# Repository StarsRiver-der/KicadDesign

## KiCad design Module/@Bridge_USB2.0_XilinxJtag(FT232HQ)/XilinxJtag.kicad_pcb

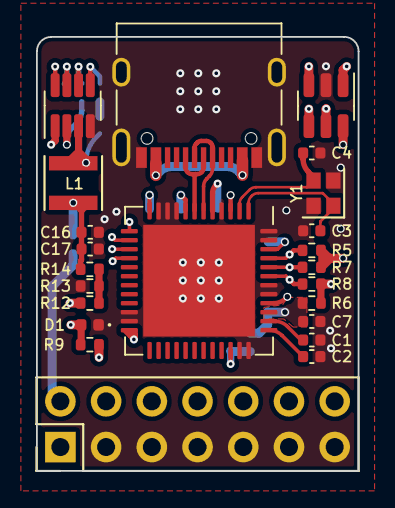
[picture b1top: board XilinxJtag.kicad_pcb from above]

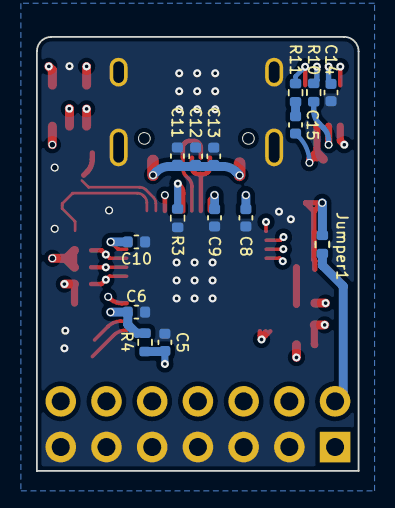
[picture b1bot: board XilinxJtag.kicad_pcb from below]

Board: 4 copper layers, 17.9 x 24.1 mm, 38 parts (15 on the bottom side), 29 nets.

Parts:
C1, C2, C5, C7, C9, C10, C12, C14, C15: 0.1uF; C_0402_1005Metric
C3, C4: 27pF; C_0402_1005Metric
C6, C8, C11, C13, C16, C17: 10uF; C_0402_1005Metric
D1: LED; LED_0402_1005Metric
J1: USB-C16PSMT01; USB_C_Receptacle_XKB_U262-16XN-4BVC11
J2: Conn_01x06_Male; PinHeader_2x07_P2.54mm_Vertical
Jumper1: Jumper; R_0402_1005Metric
L1: 4.7uF; L_Taiyo-Yuden_NR-30xx
R3: 12K; R_0402_1005Metric
R4, R5, R6, R7: 10K; R_0402_1005Metric
R8: 2K; R_0402_1005Metric
R9: 3K; R_0402_1005Metric
R10: 1M; R_0402_1005Metric
R11: 20R; R_0402_1005Metric
R12: 51K; R_0402_1005Metric
R13: 13K; R_0402_1005Metric
R14: 41.2K; R_0402_1005Metric
U1: FT232H; QFN-48-1EP_8x8mm_P0.5mm_EP6.2x6.2mm
U2: 93LC56BxxOT; SOT-23-6
U3: mp9442; TSOT-23-8
Y1: 12M; Crystal_SMD_2016-4Pin_2.0x1.6mm

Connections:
3.3V: C16.1, C17.1, Jumper1.2, L1.2, R14.1
+3V3: C6.1, C7.1, C8.1, C9.1, C10.1, R4.2, R5.1, R6.1, R7.1, U1.3 (VPHY), U1.8 (VPLL), U1.12 (VCCIO), U1.24 (VCCIO), U1.39 (VCCD), U1.46 (VCCIO), U2.6 (VCC)
DM: J1.A7 (DN1), J1.B7 (DN2), U1.6 (DM)
DP: J1.A6 (DP1), J1.B6 (DP2), U1.7 (DP)
EEP_CLK: R7.2, U1.44 (EECLK), U2.4 (CLK)
EEP_CS: R5.2, U1.45 (EECS), U2.5 (CS)
EEP_D: R8.2, U1.43 (EEDATA), U2.3 (DI)
unnamed: C1.1, U1.38 (VCCCORE)
unnamed: C2.1, U1.37 (VCCA)
unnamed: C3.2, U1.1 (XCSI), Y1.1
unnamed: C4.2, U1.2 (XCSO), Y1.3
unnamed: C14.1, U3.7 (VCC)
unnamed: C15.1, R11.1
unnamed: C15.2, L1.1, U3.3 (SW)
unnamed: D1.2 (A), R9.1, U3.1 (PG)
unnamed: J2.2, Jumper1.1
unnamed: R3.1, U1.5 (REF)
unnamed: R6.2, R8.1, U2.1 (DO)
unnamed: R10.1, U3.6 (EN)
unnamed: R11.2, U3.5 (BST)
unnamed: R12.1, R13.2, R14.2
unnamed: R12.2, U3.8 (FB)
RESET: C5.1, R4.1, U1.34 (~RESET)
TCK: J2.6, U1.13 (ADBUS0)
TDI: J2.10, U1.14 (ADBUS1)
TDO: J2.8, U1.15 (ADBUS2)
TMS: J2.4, U1.16 (ADBUS3)
VBUS: C11.1, C12.1, C13.1, J1.A4 (VBUS), J1.A9 (VBUS), J1.B4 (VBUS), J1.B9 (VBUS), R9.2, R10.2, U1.40 (VREGIN), U3.2 (IN)
VSS: C1.2, C2.2, C3.1, C4.1, C5.2, C6.2, C7.2, C8.2, C9.2, C10.2, C11.2, C12.2, C13.2, C14.2, C16.2, C17.2, D1.1 (K), J1.A1 (GND), J1.A12 (GND), J1.B1 (GND), J1.B12 (GND), J1.S1 (SHIELD), J2.3, J2.5, J2.7, J2.9, J2.11, J2.13, R3.2, R13.1, U1.4 (AGND), U1.9 (AGND), U1.10 (GND), U1.11 (GND), U1.22 (GND), U1.23 (GND), U1.35 (GND), U1.36 (GND), U1.41 (AGND), U1.42 (TEST), U1.47 (GND), U1.48 (GND), U1.49 (EP), U2.2 (GND), U3.4 (GND), Y1.2, Y1.4

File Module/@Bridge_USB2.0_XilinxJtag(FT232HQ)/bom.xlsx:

标号 | 数量/板 | 值 | 备注 | 封装 | 数量 | 单价 | 总价
C1, C2, C5, C7, C9, C10, C12, C14, C15 | 9 | 0.1uF |  | 0402 | 100 | 0 | 0
C3, C4 | 2 | 27pF |  | 0402 | 100 | 0 | 0
C6, C8, C11, C13, C16, C17 | 6 | 10uF |  | 0402 | 100 | 0 | 0
D1 | 1 | LED |  | 0402 | 100 | 0 | 0
L1 | 1 | 4.7uF |  | NR3015 | 20 | 0 | 0
R0 | 1 | 0R |  | 0402 | 100 | 0 | 0
R3 | 1 | 12K |  | 0402 | 100 | 0 | 0
R4, R5, R6, R7 | 4 | 10K |  | 0402 | 100 | 0 | 0
R8 | 1 | 2K |  | 0402 | 100 | 0 | 0
R9 | 1 | 3K |  | 0402 | 100 | 0 | 0
R10 | 1 | 1M |  | 0402 | 100 | 0 | 0
R11 | 1 | 20R |  | 0402 | 100 | 0 | 0
R12 | 1 | 51K |  | 0402 | 100 | 0 | 0
R13 | 1 | 13K |  | 0402 | 100 | 0 | 0
R14 | 1 | 41.2K |  | 0402 | 100 | 0 | 0
J1 | 1 | USB-C16PSMT01 |  | TypeC-16pin | 10 | 0 | 0
J2 | 1 | 简牛母座 14pin |  | 2.54mm, 2x7pin | 10 | 0 | 0
U1 | 1 | FT232H |  | QFN-48 | 2 | 0 | 0
U2 | 1 | 93LC56B-I/OT |  | SOT-23-6 | 5 | 0 | 0
U3 | 1 | mp9442 |  | TSOT-23-8 | 5 | 0 | 0
Y1 | 1 | 12M |  | 2Pin_2.0x1.2mm | 5 | 0 | 0

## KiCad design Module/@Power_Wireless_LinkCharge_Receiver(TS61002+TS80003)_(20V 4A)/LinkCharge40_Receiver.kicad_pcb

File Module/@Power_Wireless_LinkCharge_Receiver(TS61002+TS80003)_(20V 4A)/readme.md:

# LinkCharge无线充电接收器
提供QI1.2-15W，LinkCharge40W功率输出

# 接口
* 无线输入：Pin_5mm_2P
* 电压输出：PogoPin_4.8mm_4P

# 预览

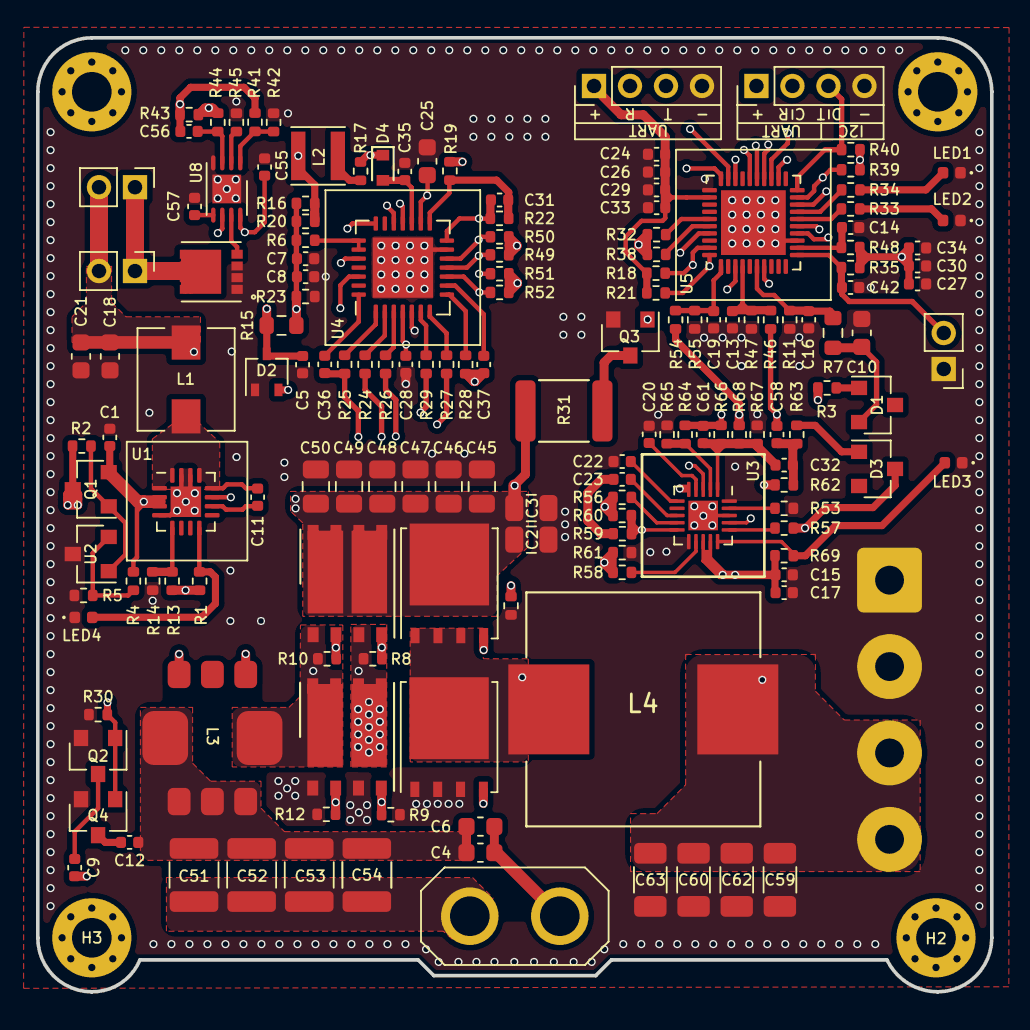
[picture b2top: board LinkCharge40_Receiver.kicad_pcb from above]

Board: 4 copper layers, 53.0 x 53.0 mm, 163 parts (0 on the bottom side), 91 nets.

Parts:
C1, C15, C20: 1uF 50V; C_0402_1005Metric
C2, C3, C45, C46, C48, C49: 22uF 50V; C_0805_2012Metric
C4, C6: 1nF 250V NP; C_0603_1608Metric
C5: 10pF 50V; C_0402_1005Metric
C7, C13, C14, C16, C17, C19, C23, C26, C28, C29, C30, C33, C42: 100nF 50V; C_0402_1005Metric
C8, C24, C27, C35: 4.7uF 25V; C_0402_1005Metric
C9, C12: 15nF 50V; C_0402_1005Metric
C10: 1nF 250V; C_0603_1608Metric
C11, C36, C37: 47nF 50V; C_0402_1005Metric
C18, C21: 22uF 16V; C_0603_1608Metric
C22: 10nF 50V; C_0402_1005Metric
C25: 10uF 25V; C_0603_1608Metric
C31: 47pF 50V; C_0402_1005Metric
C32: 1nF 50V; C_0402_1005Metric
C34: 4.7nF 100V; C_0402_1005Metric
C47, C50: 100nF 250V; C_0805_2012Metric
C51, C52: 47nF 250V; C_1210_3225Metric
C53: 10nF 250V NP; C_1210_3225Metric
C54: NP; C_1210_3225Metric
C55: 4.7uF; C_0402_1005Metric
C56: 1uF; C_0402_1005Metric
C57: 330nF; C_0402_1005Metric
C58: 22nF 50V; C_0402_1005Metric
C59, C60, C62, C63: 10uF; C_1206_3216Metric
C61: 330pF; C_0402_1005Metric
D1: BAS101S,215; SOT-23
D2: BAT54SW; SOT-323_SC-70
D3: BAS21; SOT-23
D4: 1N5819WT; D_SOD-523
H1, H2, H3, H4: MountingHole; MountingHole_2.2mm_M2_Pad_Via
J1, J6, J7: Conn_01x02_Male; PinHeader_1x02_P2.00mm_Vertical
J2, J3: I2C; PinHeader_1x04_P2.00mm_Vertical
J4: I2C; SolderWire-0.75sqmm_1x04_P4.8mm_D1.25mm_OD2.3mm
J5: COIL 24uH; AMASS_XT30U-F_1x02_P5.0mm_Vertical
L1: 4.7uH; L_Wuerth_HCI-5040
L2: 1uF; L_Taiyo-Yuden_NR-30xx
L3: PA1005.100NLT; PA1005
L4: 22uH; L_Wuerth_HCI-1350
LED1, LED2, LED3, LED4: LED; LED_0402_1005Metric
NCP15XW153J03RC1: Thermistor_NTC; R_0402_1005Metric
Q1, Q2, Q3, Q4: 2N7002; SOT-23
Q5: BSC100N06L; TDSON-8-1
Q6: BSC028N06L; TDSON-8-1
R1, R69: 5.1K; R_0402_1005Metric
R2, R5, R14, R18, R19, R21, R22, R32, R35, R39, R40, R47, R48, R55, R57, R62: 10K; R_0402_1005Metric
R3, R20, R23: 7.5K; R_0402_1005Metric
R4, R54: 133K; R_0402_1005Metric
R6, R25, R28, R49, R50, R51, R52: 0R; R_0402_1005Metric
R7: 100K; R_0603_1608Metric
R8, R9, R10, R12, R60, R61: 20K; R_0402_1005Metric
R11: 1.5K; R_0402_1005Metric
R13: 47K; R_0402_1005Metric
R15: 20R; R_0603_1608Metric
R16, R42: 200K; R_0402_1005Metric
R17, R24, R26, R27, R29, R56, R58: 1R; R_0402_1005Metric
R30: 100K; R_0402_1005Metric
R31: 200R; R_1812_4532Metric
R33, R34: 150R; R_0402_1005Metric
R38: 4.7K; R_0402_1005Metric
R41: 33K; R_0402_1005Metric
R43, R45: 12.4K; R_0402_1005Metric
R44: 5.1M; R_0402_1005Metric
R46: 75K; R_0402_1005Metric
R53: 715K; R_0402_1005Metric
R59: 3R3; R_0402_1005Metric
R63: 4.99K; R_0402_1005Metric
R64: 9.09K; R_0402_1005Metric
R65, R67: 1K; R_0402_1005Metric
R66: 34K; R_0402_1005Metric
R68: 499K; R_0402_1005Metric
U1: TS30041; QFN-16-1EP_3x3mm_P0.5mm_EP1.7x1.7mm
U2: TL431DBZ; SOT-23
U3: SC506; QFN-20-1EP_3x3mm_P0.4mm_EP1.65x1.65mm
U4: TS61002; QFN-28-1EP_5x5mm_P0.5mm_EP3.35x3.35mm
U5: TS80003; QFN-40-1EP_5x5mm_P0.4mm_EP3.6x3.6mm
U6, U7: IPG20N06S4L-11; Infineon_PG-TISON-8-2-2
U8: max31740; TDFN-8-1EP_3x2mm_P0.5mm_EP1.80x1.65mm
U9: CSD16406Q3

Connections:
+3V3: C24.1, C26.1, C29.1, C33.1, D2.2, D4.1 (K), J2.1, J3.1, R17.1, R18.1, R21.1, R39.1, R40.1, U5.15 (VDD), U5.32 (VDD)
+5V: C15.2, C17.2, C18.1, C21.1, C25.1, C28.1, C55.1, C56.1, J6.2, J7.2, L1.2, R1.2, R13.2, R41.2, R43.1, R69.2, U3.3 (VDDA), U3.13 (VDDP), U3.14 (PSV), U4.4 (VCCG), U4.16 (LDO_EN), U8.6 (D0), U8.8 (VDD)
ACMPREF: C14.1, R48.1, U5.12 (ACMPREF)
AC_I: C16.1, R7.1, R11.1, U5.6 (AC_I)
AC_I_1: R19.1, U4.19 (RA), U5.7 (AC_I_1)
AC_I_2: C31.2, R22.2, U4.14 (VOUTA), U5.3 (AC_I_2)
COIL-: C51.1, C52.1, C53.1, C54.1, J5.1, R3.2
DC_V: C13.2, R46.1, R47.2, U5.4 (DC_V)
EN_DRV: U4.26 (DRV_EN), U5.18 (DRV_EN)
EN_GAIN: R32.2, R38.2, U4.24 (GAIN)
EN_LOAD: U3.17 (EN), U5.26 (EN_LOAD)
EN_MOD: Q2.1 (G), Q4.1 (G), R30.1, U5.25 (EN_MOD)
GND: C1.2, C2.1, C3.1, C5.1, C7.2, C8.2, C10.2, C13.1, C14.2, C15.1, C16.2, C17.1, C18.2, C19.1, C20.1, C21.2, C22.1, C24.2, C25.2, C26.2, C27.2, C28.2, C29.2, C30.2, C33.2, C34.2, C35.2, C42.2, C45.1, C46.1, C47.1, C48.1, C49.1, C50.1, C55.2, C57.2, C59.1, C60.1, C62.1, C63.1, D2.1, J1.1, J2.4, J3.4, J4.1, J4.2, LED1.1 (K), LED2.1 (K), LED3.1 (K), LED4.1 (K), NCP15XW153J03RC1.2, Q2.2 (S), Q3.2 (S), Q4.2 (S), Q6.1 (S), Q6.2 (S), Q6.3 (S), R5.2, R9.1, R11.2, R12.1, R14.1, R23.1, R30.2, R42.1, R45.2, R47.1, R53.1, R55.1, R61.2, R65.2, R67.2, U1.4 (GND), U1.14 (GND), U1.15 (GND), U1.17 (GND), U2.3 (A), U3.11 (PGND), U3.18 (AGND), U3.20 (ENL), U3.21 (EP), U4.5 (PGND), U4.13 (AGND), U4.29 (PAD), U5.13 (AVSS), U5.31 (VSS), U5.41 (PAD), U7.1, U7.3, U8.4 (GND), U8.9 (EP), U9.1, U9.2, U9.3
HT: C2.2, C3.2, C45.2, C46.2, C47.2, C48.2, C49.2, C50.2, Q1.3 (D), Q5.5 (D), R2.1, R31.1, R54.2, R68.2, U3.5 (VIN), U6.5, U6.6, U6.7, U6.8
ISENSE: C5.2, D2.3, L3.3, R15.2, U4.21 (VIN)
MIN_LD: Q3.1 (G), U5.37 (EN_MINLD)
unnamed: C1.1, Q1.2 (S), R4.1, U1.2 (VCC), U1.3 (VCC), U1.11 (VCC)
unnamed: C9.2, Q2.3 (D)
unnamed: C10.1, D1.2, R7.2
unnamed: C11.1, U1.10 (BST)
unnamed: C11.2, L1.1, U1.1 (VSW), U1.12 (VSW), U1.13 (VSW), U1.16 (VSW)
unnamed: C12.2, Q4.3 (D)
unnamed: C20.2, U3.4 (VLDO)
unnamed: C22.2, U3.6 (SS)
unnamed: C23.1, U3.8 (BST)
unnamed: C23.2, R59.2
unnamed: C31.1, R19.2, R22.1, U4.15 (CA)
unnamed: C32.1, C61.1, R66.2, R67.1, R68.1, U3.1 (FB)
unnamed: C32.2, C58.1, R62.1, R63.1
unnamed: C35.1, D4.2 (A), U4.17 (VLDO)
unnamed: C36.1, U4.28 (VB1)
unnamed: C37.1, U4.9 (VB2)
unnamed: C37.2, L3.8, R10.1, R28.2, U6.1, U7.7, U7.8
unnamed: C56.2, R44.2, U8.3 (SENSE)
unnamed: C57.1, U8.5 (FREQ)
unnamed: D1.1, R3.1
unnamed: D3.1 (A), R63.2
unnamed: D3.3 (K), L4.1, Q5.1 (S), Q5.2 (S), Q5.3 (S), Q6.5 (D), R57.1, R59.1, R60.2, R62.2, U3.10 (LX)
unnamed: J2.2, R39.2, U5.19 (I2C|SCL)
unnamed: J2.3, R40.2, U5.20 (I2C|SDA)
unnamed: J3.2, R18.2, U5.39 (BT|RX)
unnamed: J3.3, R21.2, U5.40 (BT|TX)
unnamed: J6.1, J7.1, U9.5, U9.6, U9.7, U9.8
unnamed: L2.2, R17.2
unnamed: LED1.2 (A), R34.2
unnamed: LED2.2 (A), R33.2
unnamed: LED3.2 (A), R69.1, U3.15 (PG)
unnamed: LED4.2 (A), R1.1, U1.8 (PG)
unnamed: NCP15XW153J03RC1.1, R43.2, R44.1
unnamed: Q1.1 (G), R2.2, U2.1 (K)
unnamed: Q3.3 (D), R31.2
unnamed: Q5.4 (G), R56.1, R60.1
unnamed: Q6.4 (G), R58.1, R61.1
unnamed: R4.2, R5.1, U2.2 (REF)
unnamed: R6.1, U4.22 (CB), U4.23 (VOUTB)
unnamed: R10.2, R27.2, U6.2
unnamed: R12.2, R29.2, U7.2
unnamed: R13.1, R14.2, U1.5 (FB)
unnamed: R24.1, U4.2 (HO1)
unnamed: R8.2, R24.2, U6.4
unnamed: R25.1, U4.1 (VS1)
unnamed: R26.1, U4.3 (LO1)
unnamed: R9.2, R26.2, U7.4
unnamed: R27.1, U4.7 (HO2)
unnamed: R28.1, U4.8 (VS2)
unnamed: R29.1, U4.6 (LO2)
unnamed: R32.1, U5.35 (AC_GAIN1)
unnamed: R33.1, U5.16 (LEDG)
unnamed: R34.1, U5.17 (LEDB)
unnamed: R38.1, U5.36 (AC_GAIN2)
unnamed: R41.1, R42.2, U8.1 (Dmin)
unnamed: R45.1, U8.2 (SLOPE)
unnamed: R49.1, R50.1, U5.22 (ACMP1_OUT)
unnamed: R51.1, R52.1, U5.28 (ACMP2_OUT)
unnamed: R53.2, U3.19 (TON)
unnamed: R56.2, U3.9 (DH)
unnamed: R57.2, U3.16 (LIMI)
unnamed: R58.2, U3.12 (DL)
unnamed: R64.2, R65.1, U3.2 (VOUT)
unnamed: U8.7 (PWM_OUT), U9.4
PDC_V: C19.2, R54.1, R55.2, U5.1 (PDC_V)
PWM1_H: R49.2, U4.11 (HS1ON), U5.23 (PWM1|H)
PWM1_L: R52.2, U4.10 (LS1ON), U5.24 (PWM1|L)
PWM2_H: R51.2, U4.18 (HS2ON), U5.30 (PWM2|H)
PWM2_L: R50.2, U4.12 (LS2ON), U5.29 (PWM2|L)
TEMP: C42.1, J1.2, R35.1, U5.11 (TEMP)
VAC1: C4.1, C6.1, C9.1, C36.2, J5.2, R8.1, R25.2, U6.3, U7.5, U7.6
VAC2: C4.2, C6.2, C12.1, C51.2, C52.2, C53.2, C54.2, L3.4, L3.5, L3.6, L3.7
VACC_MID: C7.1, C8.1, L3.1, R6.2, R15.1, R16.1, R20.1, R23.2
VDC: C58.2, C59.2, C60.2, C61.2, C62.2, C63.2, J4.3, J4.4, L4.2, R46.2, R64.1, R66.1
VDDA: C27.1, C30.1, C34.1, L2.1, R16.2, R20.2, R35.2, R48.2, U5.14 (AVDD)

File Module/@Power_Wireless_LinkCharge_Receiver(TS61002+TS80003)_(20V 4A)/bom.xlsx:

标号 | 数量/板 | 值 | 封装 | 数量 | 单价 | 总价
C1, C15, C20 | 3 | 1uF 50V | 0402 | 100 | 0 | 0
C2, C3, C45, C46, C48, C49 | 6 | 22uF 50V | 0805 | 100 | 0 | 0
C4, C6 | 2 | 1nF 250V | 0603 | 100 | 0 | 0
C5 | 1 | 10pF 50V | 0402 | 100 | 0 | 0
C7, C13, C14, C16, C17, C19, C23, C26, C28, C29, C30, C33, C42 | 13 | 100nF 50V | 0402 | 100 | 0 | 0
C8, C24, C27, C35 | 4 | 4.7uF 25V | 0402 | 100 | 0 | 0
C9, C12 | 2 | 15nF 50V | 0402 | 100 | 0 | 0
C10 | 1 | 1nF 250V | 0603 | 100 | 0 | 0
C11, C36, C37 | 3 | 47nF 50V | 0402 | 100 | 0 | 0
C18, C21 | 2 | 22uF 16V | 0603 | 100 | 0 | 0
C22 | 1 | 10nF 50V | 0402 | 100 | 0 | 0
C25 | 1 | 10uF 25V | 0603 | 100 | 0 | 0
C31 | 1 | 47pF 50V | 0402 | 100 | 0 | 0
C32 | 1 | 1nF 50V | 0402 | 100 | 0 | 0
C34 | 1 | 4.7nF 100V | 0402 | 100 | 0 | 0
C47, C50 | 2 | 100nF 250V | 0805 | 100 | 0 | 0
C51, C52 | 2 | 47nF 250V | 1210 | 100 | 0 | 0
C53 | 1 | 10nF 250V | 1210 | 100 | 0 | 0
C54 | 1 | NP | 1210 | 100 | 0 | 0
C55 | 1 | 4.7uF 25V | 0402 | 100 | 0 | 0
C56 | 1 | 1uF 25V | 0402 | 100 | 0 | 0
C57 | 1 | 330nF 25V | 0402 | 100 | 0 | 0
C58 | 1 | 22nF 50V | 0402 | 100 | 0 | 0
C59, C60, C62, C63 | 4 | 10uF 50V | 1206 | 100 | 0 | 0
C61 | 1 | 330pF 50V | 0402 | 100 | 0 | 0
L1 | 1 | 4.7uH | 5040 | 20 | 0 | 0
L2 | 1 | 1uH | 3014 | 20 | 0 | 0
L3 | 1 | PA1005.100NLT | PA1005 | 10 | 0 | 0
L4 | 1 | 22uH | 1250 | 10 | 0 | 0
LED1, LED2, LED3, LED4 | 4 | LED | 0402 | 100 | 0 | 0
R1, R69 | 2 | 5.1K | 0402 | 100 | 0 | 0
R2, R5, R14, R18, R19, R21, R22, R32, R35, R39, R40, R47, R48, R55, R57, R62 | 16 | 10K | 0402 | 100 | 0 | 0
R3, R20, R23 | 3 | 7.5K | 0402 | 100 | 0 | 0
R4, R54 | 2 | 133K | 0402 | 100 | 0 | 0
R6, R25, R28, R49, R50, R51, R52 | 7 | 0R | 0402 | 100 | 0 | 0
R7 | 1 | 100K | 0603 | 100 | 0 | 0
R8, R9, R10, R12, R60, R61 | 6 | 20K | 0402 | 100 | 0 | 0
R11 | 1 | 1.5K | 0402 | 100 | 0 | 0
R13 | 1 | 47K | 0402 | 100 | 0 | 0
R15 | 1 | 20R | 0603 | 100 | 0 | 0
R16, R42 | 2 | 200K | 0402 | 100 | 0 | 0
R17, R24, R26, R27, R29, R56, R58 | 7 | 1R | 0402 | 100 | 0 | 0
R30 | 1 | 100K | 0402 | 100 | 0 | 0
R31 | 1 | 200R | 1812 | 100 | 0 | 0
R33, R34 | 2 | 150R | 0402 | 100 | 0 | 0
R38 | 1 | 4.7K | 0402 | 100 | 0 | 0
R41 | 1 | 33K | 0402 | 100 | 0 | 0
R43, R45 | 2 | 12.4K | 0402 | 100 | 0 | 0
R44 | 1 | 5.1M | 0402 | 100 | 0 | 0
R46 | 1 | 75K | 0402 | 100 | 0 | 0
R53 | 1 | 715K | 0402 | 100 | 0 | 0
R59 | 1 | 3R3 | 0402 | 100 | 0 | 0
R63 | 1 | 4.99K | 0402 | 100 | 0 | 0
R64 | 1 | 9.09K | 0402 | 100 | 0 | 0
R65, R67 | 2 | 1K | 0402 | 100 | 0 | 0
R66 | 1 | 34K | 0402 | 100 | 0 | 0
R68 | 1 | 499K | 0402 | 100 | 0 | 0
TR1 | 1 | NCP15XW153J03RC1 | 0402 | 20 | 0 | 0
D1 | 1 | BAS101S,215 | SOT-23 | 20 | 0 | 0
D2 | 1 | BAT54SW | SOT-323_SC-70 | 20 | 0 | 0
D3 | 1 | BAS21-03W | SOT-23 | 20 | 0 | 0
D4 | 1 | RB521S-30C | SOT-523 | 20 | 0 | 0
Q1, Q2, Q3, Q4 | 4 | 2N7002 | SOT-23 | 20 | 0 | 0
Q5 | 1 | BSC100N06L | TDSON-8-1 | 10 | 0 | 0
Q6 | 1 | BSC028N06L | TDSON-8-1 | 10 | 0 | 0
U2 | 1 | TL431DBZ | SOT-23 | 20 | 0 | 0
U1 | 1 | TS30041 | QFN-16-1EP_3x3mm_P0.5mm | 5 | 0 | 0
U3 | 1 | SC506 | QFN-20-1EP_3x3mm_P0.4mm | 5 | 0 | 0
U4 | 1 | TS61002 | QFN-28-1EP_5x5mm_P0.5mm | 5 | 0 | 0
U5 | 1 | TS80003 | QFN-40-1EP_5x5mm_P0.4mm | 5 | 0 | 0
U6, U7 | 2 | IPG20N06S4L-11 | PG-TISON-8-2-2 | 10 | 0 | 0
U8 | 1 | max31740 | TDFN-8-1EP_3x2mm_P0.5mm | 5 | 0 | 0
U9 | 1 | CSD16406Q3 |  | 5 | 0 | 0

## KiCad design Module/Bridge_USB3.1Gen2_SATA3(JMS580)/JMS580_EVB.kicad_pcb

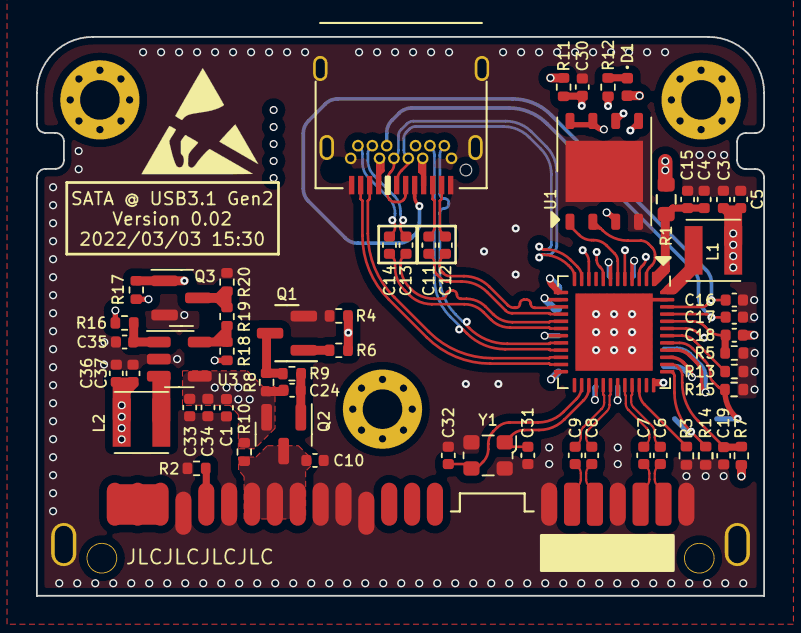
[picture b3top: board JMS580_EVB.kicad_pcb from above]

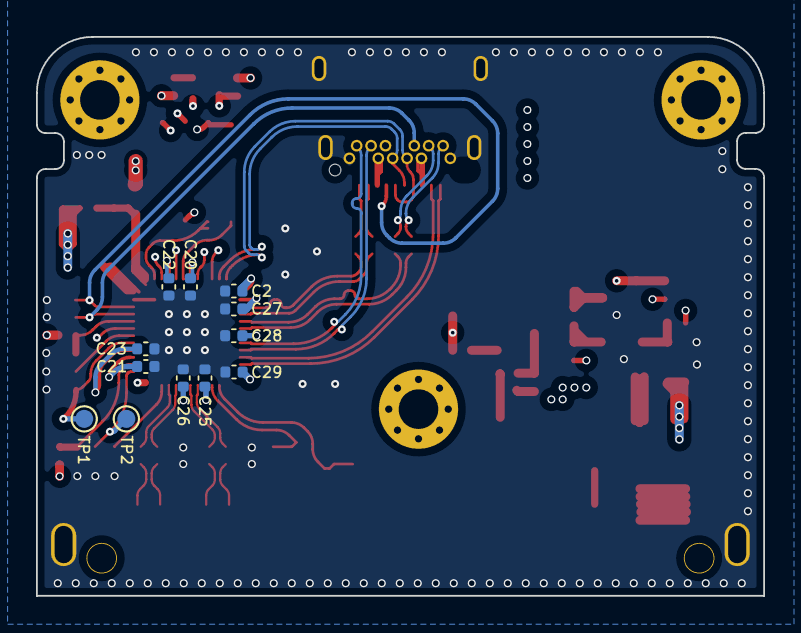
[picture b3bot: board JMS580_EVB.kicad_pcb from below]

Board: 4 copper layers, 40.4 x 31.1 mm, 75 parts (12 on the bottom side), 57 nets.

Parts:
C1, C10: 4.7uF; C_0402_1005Metric
C2, C18, C19, C24, C30, C35: 1uF; C_0402_1005Metric
C3, C4, C5, C33, C36: 10uF; C_0402_1005Metric
C6, C7, C8, C9: 10nF; C_0402_1005Metric
C11, C12, C13, C14, C15, C20, C21, C22, C23, C25, C26, C27, C28, C29, C34, C37: 100nF; C_0402_1005Metric
C16, C17: 330pF; C_0402_1005Metric
C31, C32: 20pF; C_0402_1005Metric
D1: LED; LED_0402_1005Metric
H1, H2, H3: MountingHole; MountingHole_2.2mm_M2_Pad_Via
H4: Symbol; ESD-Logo_6.6x6mm_SilkScreen
J1: ATA-A; SATA-22P-M
J2: USB_C_Receptacle; USB-C_24p
L1: 4R7 / NS; L_Neosid_SMS-ME3015
L2: 3R3; L_Neosid_SMS-ME3015
Q1: MMBT3904LT1G(1AM); SOT-23
Q2: AO3401A; SOT-23
Q3: AO3400A; SOT-23
R1: 0R; R_0603_1608Metric
R2: 10K; R_0402_1005Metric
R3: 12K; R_0402_1005Metric
R4, R5, R6, R13, R17: 4.7K; R_0402_1005Metric
R7, R16, R20: 510K; R_0402_1005Metric
R8, R12: 1K; R_0402_1005Metric
R9: 0R; R_0402_1005Metric
R10: 0R / NS; R_0402_1005Metric
R11: 2R2; R_0402_1005Metric
R14, R15, R18: 100K; R_0402_1005Metric
R19: 127K; R_0402_1005Metric
TP1, TP2: TestPoint; TestPoint_Pad_D1.0mm
U1: W25Q32JVZP; WSON-8-1EP_6x5mm_P1.27mm_EP3.4x4.3mm
U2: JMS580; QFN-48-1EP_6x6mm_P0.4mm_EP4.3x4.3mm
U3: FP6381A; SOT-23-5
Y1: Crystal_GND24; Oscillator_SMD_ECS_2520MV-xxx-xx-4Pin_2.5x2.0mm

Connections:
1V0: C3.1, C5.1, C22.1, C23.1, C25.1, C26.1, C27.1, C28.1, C29.1, C36.2, C37.2, L1.1, L2.1, R18.2, U2.4 (VCCK), U2.14 (AVDDL), U2.19 (AVDDL), U2.24 (AVDDL), U2.28 (AVDDL), U2.31 (AVDDL), U2.40 (VCCK)
/SA_RXX+: C8.2, J1.S5 (SA_RX-)
/SA_RXX-: C9.2, J1.S6 (SA_RX+)
/SA_TXX+: C6.2, J1.S2 (SA_TX+)
/SA_TXX-: C7.2, J1.S3 (SA_TX-)
/SS_TX1X+: C12.2, J2.A2 (TX1+)
/SS_TX1X-: C11.2, J2.A3 (TX1-)
/SS_TX2X+: C14.2, J2.B2 (TX2+)
/SS_TX2X-: C13.2, J2.B3 (TX2-)
CC1: C16.2, J2.A5 (CC1), U2.46 (CC1)
CC2: C17.2, J2.B5 (CC2), U2.45 (CC2)
D+: J2.A6 (D+), J2.B6 (D+), U2.12 (D+)
D-: J2.A7 (D-), J2.B7 (D-), U2.11 (D-)
DAS: J1.P11 (Reserve), R2.1
GND: C1.1, C2.2, C3.2, C4.1, C5.2, C10.2, C15.1, C16.1, C17.1, C19.1, C20.2, C21.2, C22.2, C23.2, C25.2, C26.2, C27.2, C28.2, C29.2, C30.1, C31.2, C32.2, C33.1, C34.1, C35.2, C36.1, C37.1, J1.Mt1 (GND), J1.Mt2 (GND), J1.P4 (GND), J1.P5 (GND), J1.P6 (GND), J1.P10 (GND), J1.P12 (GND), J1.S1 (GND), J1.S4 (GND), J1.S7 (GND), J2.A1 (GND), J2.A12 (GND), J2.B1 (GND), J2.B12 (GND), J2.S1 (SHIELD), Q1.2 (E), Q3.2 (S), R2.2, R3.2, R4.1, R5.2, R13.2, R14.2, R15.2, R20.1, U1.4 (GND), U1.9 (EP), U2.47 (GND), U2.49 (EP), U3.2 (GND), Y1.2, Y1.4
GPIO0: U1.2 (SO), U2.2 (GPIO0)
GPIO1: U1.6 (SCK), U2.3 (GPIO1)
GPIO2: U1.5 (SI), U2.5 (GPIO2)
GPIO3: U1.1 (~CS), U2.6 (GPIO3)
GPIO4: R12.1, U2.8 (GPIO4)
GPIO7: R4.2, R6.1, U2.36 (GPIO7)
GPIO8: R14.1, TP2.1, U2.37 (GPIO8/UAO)
GPIO9: R15.1, TP1.1, U2.41 (GPIO9/UAI)
GPIO10: R13.1, U2.42 (GPIO10)
GPIO11: Q3.1 (G), R17.1, U2.43 (GPIO11)
HDD5V: C10.1, J1.P7 (5V), J1.P8 (5V), J1.P9 (5V), Q2.3 (D), R10.2
LDO_33: C2.1, C18.2, C20.1, C21.1, R7.1, R17.2, U1.3 (~WP), U1.7 (HOLD), U1.8 (VCC), U2.7 (VCCO), U2.13 (AVDD33_O), U2.39 (VCCO)
LXO: L1.2, U2.48 (LXO)
unnamed: C24.2, Q2.1 (G), R9.1
unnamed: C30.2, R11.2, U2.10 (VBUS)
unnamed: C31.1, U2.27 (XIN), Y1.1
unnamed: C32.1, U2.26 (XOUT), Y1.3
unnamed: C35.1, R16.1, U3.1 (EN)
unnamed: D1.1 (K), R12.2
unnamed: J1.P13 (12V), J1.P14 (12V), J1.P15 (12V)
unnamed: L2.2, U3.3 (LX)
unnamed: Q1.1 (B), R6.2
unnamed: Q1.3 (C), R8.1, R9.2
unnamed: Q3.3 (D), R19.1, R20.2
unnamed: R18.1, R19.2, U3.5 (FB)
REXT: R3.1, U2.34 (R_EXT)
RST#: C19.2, R7.2, U2.38 (RST#)
SA_RX+: C9.1, U2.29 (SARX+)
SA_RX-: C8.1, U2.30 (SARX-)
SA_TX+: C6.1, U2.33 (SATX+)
SA_TX-: C7.1, U2.32 (SATX-)
SS_RX1+: J2.B11 (RX1+), U2.20 (SSRX1+)
SS_RX1-: J2.B10 (RX1-), U2.21 (SSRX1-)
SS_RX2+: J2.A11 (RX2+), U2.23 (SSRX2+)
SS_RX2-: J2.A10 (RX2-), U2.22 (SSRX2-)
SS_TX1+: C12.1, U2.15 (SSTX1+)
SS_TX1-: C11.1, U2.16 (SSTX1-)
SS_TX2+: C14.1, U2.18 (SSTX2+)
SS_TX2-: C13.1, U2.17 (SSTX2-)
TME: C18.1, R5.1, U2.44 (TME)
VBUS: C1.2, C24.1, C33.2, C34.2, D1.2 (A), J2.A4 (VBUS), J2.A9 (VBUS), J2.B4 (VBUS), J2.B9 (VBUS), Q2.2 (S), R1.2, R8.2, R10.1, R11.1, R16.2, U3.4 (VIN)
VREG: C4.2, C15.2, R1.1, U2.1 (VREG_IN)

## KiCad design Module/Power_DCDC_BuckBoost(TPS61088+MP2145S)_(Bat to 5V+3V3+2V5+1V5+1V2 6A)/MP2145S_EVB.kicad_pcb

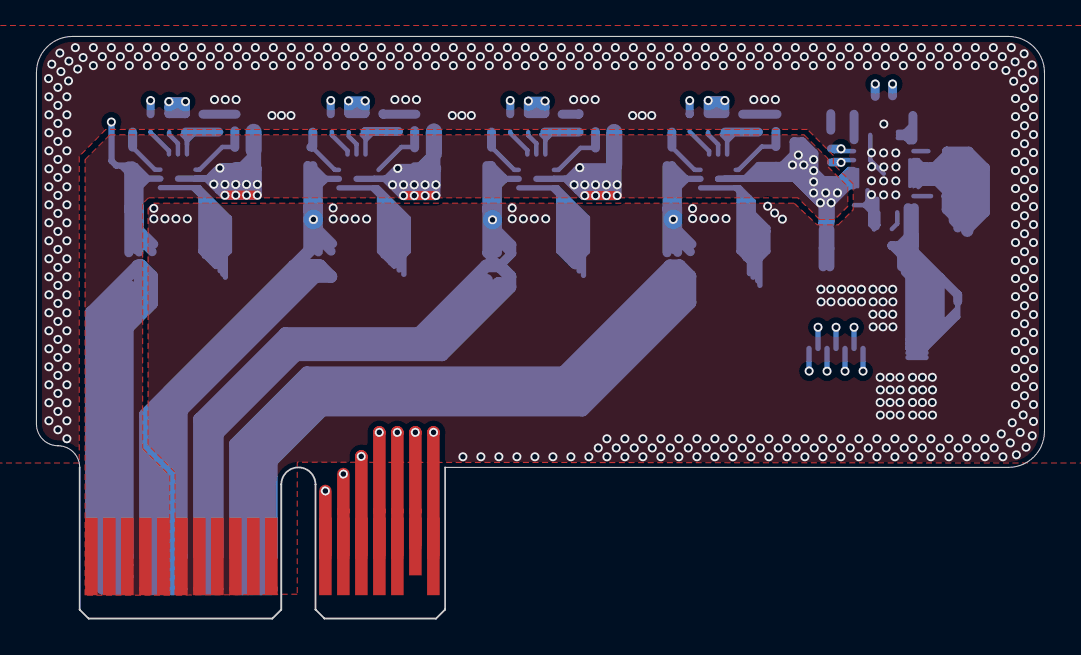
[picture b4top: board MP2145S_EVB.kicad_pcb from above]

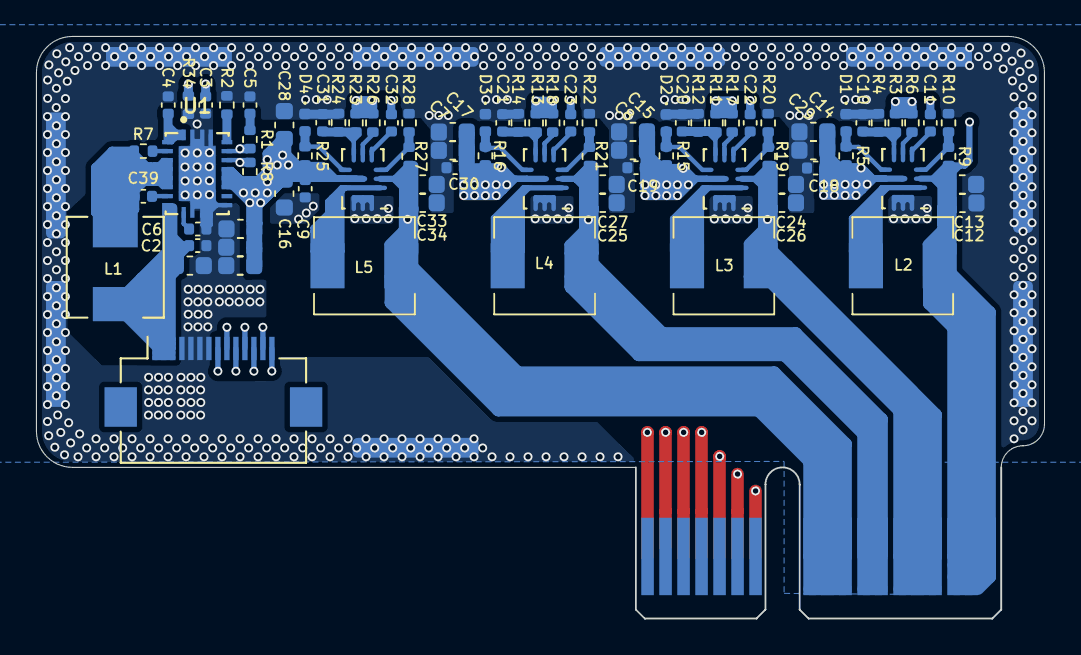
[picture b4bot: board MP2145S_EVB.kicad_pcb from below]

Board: 4 copper layers, 56.0 x 32.3 mm, 92 parts (91 on the bottom side), 47 nets.

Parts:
C1, C7, C8, C14, C15, C16, C17, C28, C29: 10uF; C_0603_1608Metric
C2, C9, C18, C19, C30, C39: 0.1uF; C_0402_1005Metric
C3: 47pF; C_0402_1005Metric
C4, C10, C20, C21, C31: 1uF; C_0402_1005Metric
C5: 1nF; C_0402_1005Metric
C6: 8.2nF; C_0402_1005Metric
C11, C22, C23, C32: NS; C_0402_1005Metric
C12, C13, C24, C25, C26, C27, C33, C34, C40, C41, C42: 22uF; C_0603_1608Metric
D1, D2, D3, D4: LED; LED_0402_1005Metric
J1: Conn_01x14; Hirose_FH12-14S-0.5SH_1x14-1MP_P0.50mm_Horizontal
J2, J3, J4, J6, J7, J8, J9, J10, J11: Conn_01x01; pad-6-1.5
L1: 1uH; L_Sunlord_MWSA0518_5.4x5.2mm
L2, L3, L4, L5: 0.47uH; L_Sunlord_MWSA0518_5.4x5.2mm
PCI1: Conn_02x18_Row_Letter_First; BUS_PCIexpress_x1
R1: 23.7K; R_0402_1005Metric
R2: 113K; R_0402_1005Metric
R3, R11, R13, R23: NS/200K; R_0402_1005Metric
R4, R6, R12, R14, R17, R18, R24, R26: 100K; R_0402_1005Metric
R5, R15, R16, R25: 2K; R_0402_1005Metric
R7: 267K; R_0402_1005Metric
R8: 220K; R_0402_1005Metric
R9, R10, R19, R21, R27: 200K; R_0402_1005Metric
R20: 133.3K; R_0402_1005Metric
R22: 63.2K; R_0402_1005Metric
R28: 44.2K; R_0402_1005Metric
R34: 69.8K; R_0402_1005Metric
U1: TPS61088RHLR; IC_TPS61088RHLR
U2, U3, U4, U5: MP214x; MP2145

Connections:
1.2V: C11.1, C12.1, C13.1, L2.2, PCI1.A1, PCI1.A2, PCI1.A3, R9.1, U2.2 (OUT)
1.5V: C22.1, C24.1, C26.1, L3.2, PCI1.A4, PCI1.A5, PCI1.A6, R19.1, U3.2 (OUT)
2.5V: C23.1, C25.1, C27.1, L4.2, PCI1.A7, PCI1.A8, R21.1, U4.2 (OUT)
3.3V: C32.1, C33.1, C34.1, L5.2, PCI1.A9, PCI1.A10, PCI1.A11, R27.1, U5.2 (OUT)
5V: C7.1, C8.1, C9.1, C14.1, C15.1, C16.1, C17.1, C18.1, C19.1, C28.1, C29.1, C30.1, C40.1, C41.1, C42.1, PCI1.B1, PCI1.B2, PCI1.B3, PCI1.B4, PCI1.B5, R3.1, R5.1, R6.1, R8.2, R11.1, R13.1, R15.1, R16.1, R17.1, R18.1, R23.1, R25.1, R26.1, U1.14 (VOUT_16), U1.15 (VOUT_14), U1.16 (VOUT_15), U2.8 (VIN), U3.8 (VIN), U4.8 (VIN), U5.8 (VIN)
BAT+: C1.1, C2.1, J1.1, J1.2, J1.3, L1.1, U1.9 (VIN)
BAT_CHG: J1.8, PCI1.B18
BAT_ISET: J1.10, PCI1.B16
BAT_PG: J1.9, PCI1.B17
GND: C1.2, C2.2, C3.2, C4.2, C5.2, C6.2, C7.2, C8.2, C9.2, C10.2, C12.2, C13.2, C14.2, C15.2, C16.2, C17.2, C18.2, C19.2, C20.2, C21.2, C24.2, C25.2, C26.2, C27.2, C28.2, C29.2, C30.2, C31.2, C33.2, C34.2, C40.2, C41.2, C42.2, D1.1 (K), D2.1 (K), D3.1 (K), D4.1 (K), J1.4, J1.5, J1.6, J1.7, J2.1, J3.1, J4.1, J6.1, J7.1, J8.1, J9.1, J10.1, J11.1, PCI1.B6, PCI1.B7, PCI1.B8, PCI1.B9, PCI1.B10, PCI1.B11, R2.2, R4.2, R10.2, R12.2, R14.2, R20.2, R22.2, R24.2, R28.2, R34.1, U1.11 (NC_11), U1.12 (NC_12), U1.20 (AGND), U1.21 (PGND), U2.10 (GND), U2.11 (GND), U2.12 (GND), U3.10 (GND), U3.11 (GND), U3.12 (GND), U4.10 (GND), U4.11 (GND), U4.12 (GND), U5.10 (GND), U5.11 (GND), U5.12 (GND)
unnamed: C3.1, R1.1, U1.18 (COMP)
unnamed: C4.1, U1.1 (VCC), U1.2 (EN)
unnamed: C5.1, R1.2
unnamed: C6.1, U1.10 (SS)
unnamed: C10.1, R3.2, R4.1, U2.6 (MODE)
unnamed: C11.2, U2.4 (Ramp)
unnamed: C20.1, R11.2, R12.1, U3.6 (MODE)
unnamed: C21.1, R13.2, R14.1, U4.6 (MODE)
unnamed: C22.2, U3.4 (Ramp)
unnamed: C23.2, U4.4 (Ramp)
unnamed: C31.1, R23.2, R24.1, U5.6 (MODE)
unnamed: C32.2, U5.4 (Ramp)
unnamed: C39.1, U1.8 (BOOT)
unnamed: C39.2, L1.2, R7.2, U1.4 (SW_7), U1.5 (SW_4), U1.6 (SW_5), U1.7 (SW_6)
unnamed: L2.1, U2.1 (SW), U2.9 (SW)
unnamed: L3.1, U3.1 (SW), U3.9 (SW)
unnamed: L4.1, U4.1 (SW), U4.9 (SW)
unnamed: L5.1, U5.1 (SW), U5.9 (SW)
unnamed: R2.1, U1.19 (ILIM)
unnamed: R6.2, U2.5 (EN)
unnamed: R7.1, U1.3 (FSW)
unnamed: R9.2, R10.1, U2.3 (FB)
unnamed: R17.2, U3.5 (EN)
unnamed: R18.2, U4.5 (EN)
unnamed: R19.2, R20.1, U3.3 (FB)
unnamed: R21.2, R22.1, U4.3 (FB)
unnamed: R26.2, U5.5 (EN)
unnamed: R27.2, R28.1, U5.3 (FB)
unnamed: R8.1, R34.2, U1.17 (FB)
PG_1.2: D1.2 (A), R5.2, U2.7 (PG)
PG_1.5: D2.2 (A), R15.2, U3.7 (PG)
PG_2.5: D3.2 (A), R16.2, U4.7 (PG)
PG_3.3: D4.2 (A), R25.2, U5.7 (PG)
REG_CHG: J1.12, PCI1.B14
REG_EN1: J1.13, PCI1.B13
REG_EN2: J1.14, PCI1.B12
REG_POWER: J1.11, PCI1.B15
